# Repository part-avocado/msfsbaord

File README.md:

# msfsbaord
A little macroboard for msfs (for hackclub)

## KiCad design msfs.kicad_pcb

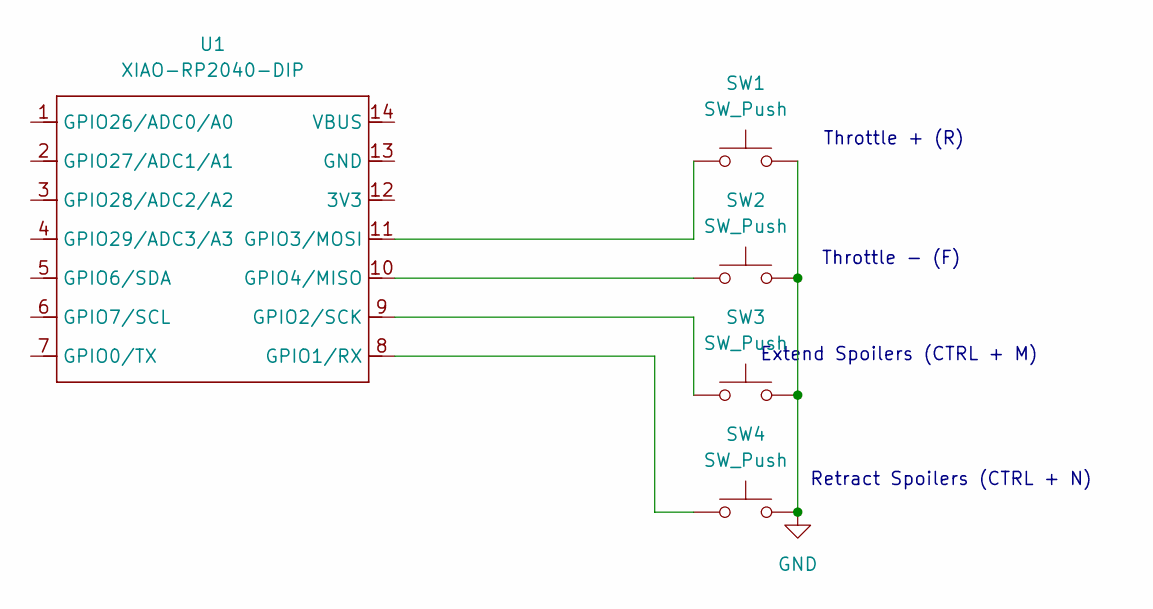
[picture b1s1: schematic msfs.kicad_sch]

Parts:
SW1, SW2, SW3, SW4: SW_Push; SW_Cherry_MX_1.00u_PCB
U1: XIAO-RP2040-DIP

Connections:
GND: SW1.2, SW2.2, SW3.2, SW4.2
unnamed: SW4.1, U1.8 (GPIO1/RX)
unnamed: SW3.1, U1.9 (GPIO2/SCK)
unnamed: SW1.1, U1.11 (GPIO3/MOSI)
unnamed: SW2.1, U1.10 (GPIO4/MISO)

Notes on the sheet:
Retract Spoilers (CTRL + N)
Throttle - (F)
Throttle + (R)
Extend Spoilers (CTRL + M)

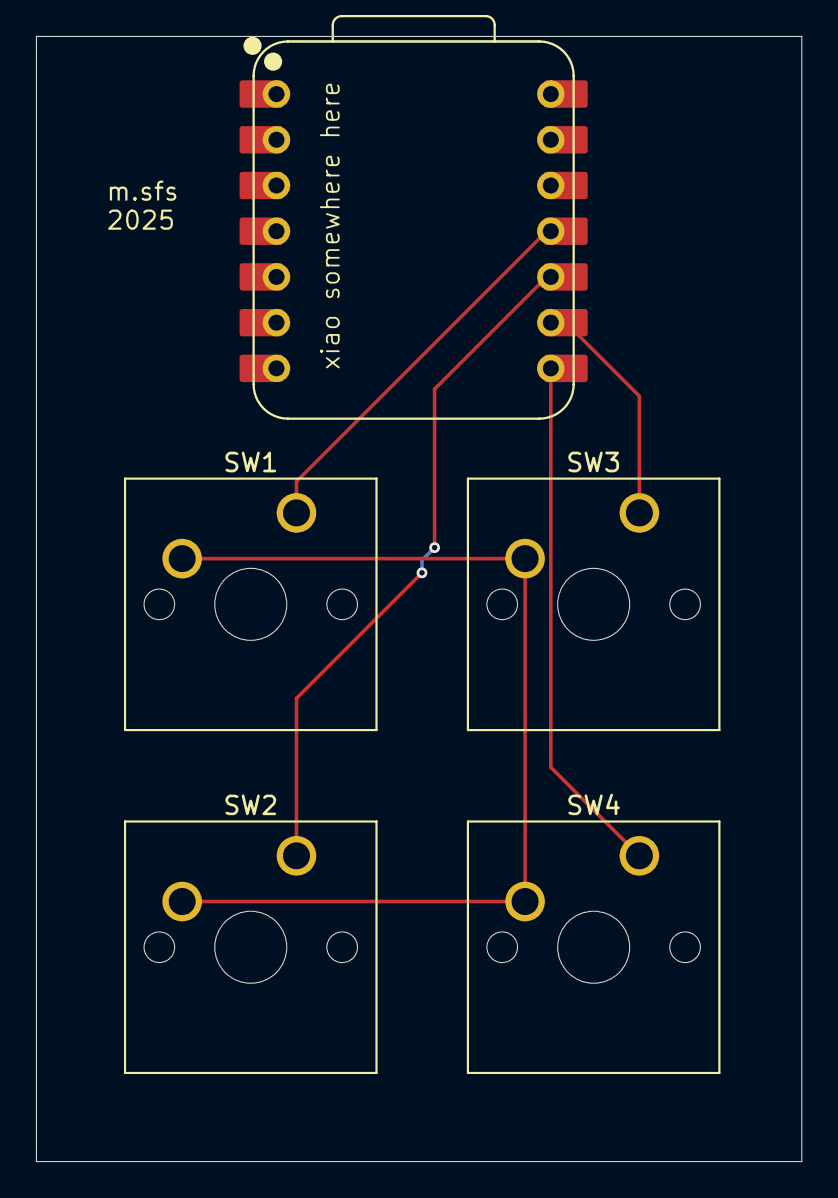
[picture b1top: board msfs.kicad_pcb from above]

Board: 2 copper layers, 42.5 x 62.5 mm, 5 parts (0 on the bottom side), 5 nets.

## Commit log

2025-11-28 init commit
2025-11-28 the board
